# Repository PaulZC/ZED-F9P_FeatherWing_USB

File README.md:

# ZED-F9P FeatherWing USB

A GNSS FeatherWing incorporating the dual-band (L1 + L2) [u-blox ZED-F9P](https://www.u-blox.com/en/product/zed-f9p-module)

The board can be used stand-alone, powered and interfaced through the USB connector:

However, it is designed to mount on top of the [Adafruit Feather M0 Adalogger](https://www.adafruit.com/products/2796)
to form a very compact dual-band PPK data logger or RTK system:

This version provides access to the ZED-F9P's USB port. The [ZED-F9P_FeatherWing](https://github.com/PaulZC/ZED-F9P_FeatherWing) is a simpler version
with fewer components and a CR1220 back-up battery but without USB.

Based extensively on the [Adafruit Ultimate GPS FeatherWing](https://www.adafruit.com/product/3133) and the
[SparkFun GPS-RTK2 Board](https://www.sparkfun.com/products/15136)

If you don't want to make your own FeatherWing and want to use the SparkFun GPS-RTK2 Board instead, you can find a tutorial showing you how to do that
[here](https://github.com/PaulZC/F9P_RAWX_Logger)

See [LEARN.md](./LEARN.md) for more details

[ASSEMBLY.md](./ASSEMBLY.md) contains instructions on how to assemble the PCB

[PAIRING.md](./PAIRING.md) contains instructions on how to configure two SparkFun Bluetooth Mate Gold boards
as a bonded pair, to provide a 115200 Baud RTCM link

The Eagle files are available in the [Eagle folder](./Eagle)

The schematic is available [here](./Schematic.PNG)

The BOM is available [here](./BOM.pdf)

The PCB thickness should be 0.8mm: see the microstrip calculations on the [SparkFun schematic](https://cdn.sparkfun.com/assets/9/a/0/0/a/Qwiic_GPS-RTK2_-_ublox_ZED-F9P.pdf)

## Arduino Code

Two versions of the Arduino code can be found in the [Arduino folder](./Arduino):

- **RAWX_Logger_F9P** is very similar to the logger I wrote for the [NEO-M8T FeatherWing](https://github.com/PaulZC/NEO-M8T_GNSS_FeatherWing) but is substantially updated for the ZED-F9P. It does all of the message configuration via UART1. **PLEASE NOTE:** this example is out-of-date as it uses the old version of the SparkFun u-blox Library.

- **RAWX_Logger_F9P_I2C** uses **version 3.1.5** of the SparkFun u-blox GNSS library to do all of the message configuration via the I2C port instead of UART1. This makes
the code more efficient as it does not need to ignore the UBX ACK messages (on UART1) and can simply stream all data from UART1 to the SD card.

You can find instructions on how to install the Arduino IDE and the required libraries [here](https://github.com/PaulZC/F9P_RAWX_Logger/blob/master/SOFTWARE.md).

The code has three 'modes': Rover, Base and Survey_In. The mode is set via pins A0 and A3 by the [RAWX Logger Switches](https://github.com/PaulZC/RAWX_Logger_Switches). The RAWX
messages are logged to SD card in all three modes for post-processing with [rtklibexplorer's](https://rtklibexplorer.wordpress.com/) version of [RTKLIB](http://rtkexplorer.com/downloads/rtklib-code/).

You will find settings in the code to help with debugging should you need it. Uncomment the line which contains **#define DEBUG** to enable them.

## Updating the ZED-F9P firmware

u-blox released [version 1.12](https://www.u-blox.com/sites/default/files/UBX_F9_100_HPG_112_ZED_F9P.a26bfd58dfd11c233f8fdba6b99adc5a.bin) of the ZED-F9P firmware
on 12th July 2019. If you bought your device(s) before then, it would be beneficial to update. The update process is straight forward and can be done through
the Tools menu in [u-center](https://www.u-blox.com/en/product/u-center) **but the update can only be done through UART1. It will fail if you try to update through USB.**

The [Arduino folder](./Arduino) contains a sketch called ZED-F9P_Echo. This will turn the Adalogger into
a simple USB to UART pass-through which you can use to update the ZED-F9P using u-center. The code runs at **9600 Baud only** so you must tick the
_Use this baudrate for update_ box and select 9600 from the drop-down list. The advice on the u-blox portal seems to be to select the _Use chip erase_ option too.

Updating at 9600 Baud is very slow, but this is the only way to prevent Baud rate changes during the update. The Echo code is very simple and does not support
baud rate changes. If you want to update more quickly, you can use (e.g.) an FTDI TTL-232R-3V3 cable to connect to the UART1 pins instead of the Adalogger.

## Acknowledgements

This project would not have been possible without the open source designs kindly provided by both Adafruit and SparkFun. Their work is gratefully acknowledged.

Adafruit invests time and resources providing this open source design, please support Adafruit and open-source hardware by purchasing products from Adafruit!

Feel like supporting open source hardware? Buy a board from SparkFun!

## Licence

Please see [LICENSE.md](./LICENSE.md) for details.

Enjoy!

**_Paul_**

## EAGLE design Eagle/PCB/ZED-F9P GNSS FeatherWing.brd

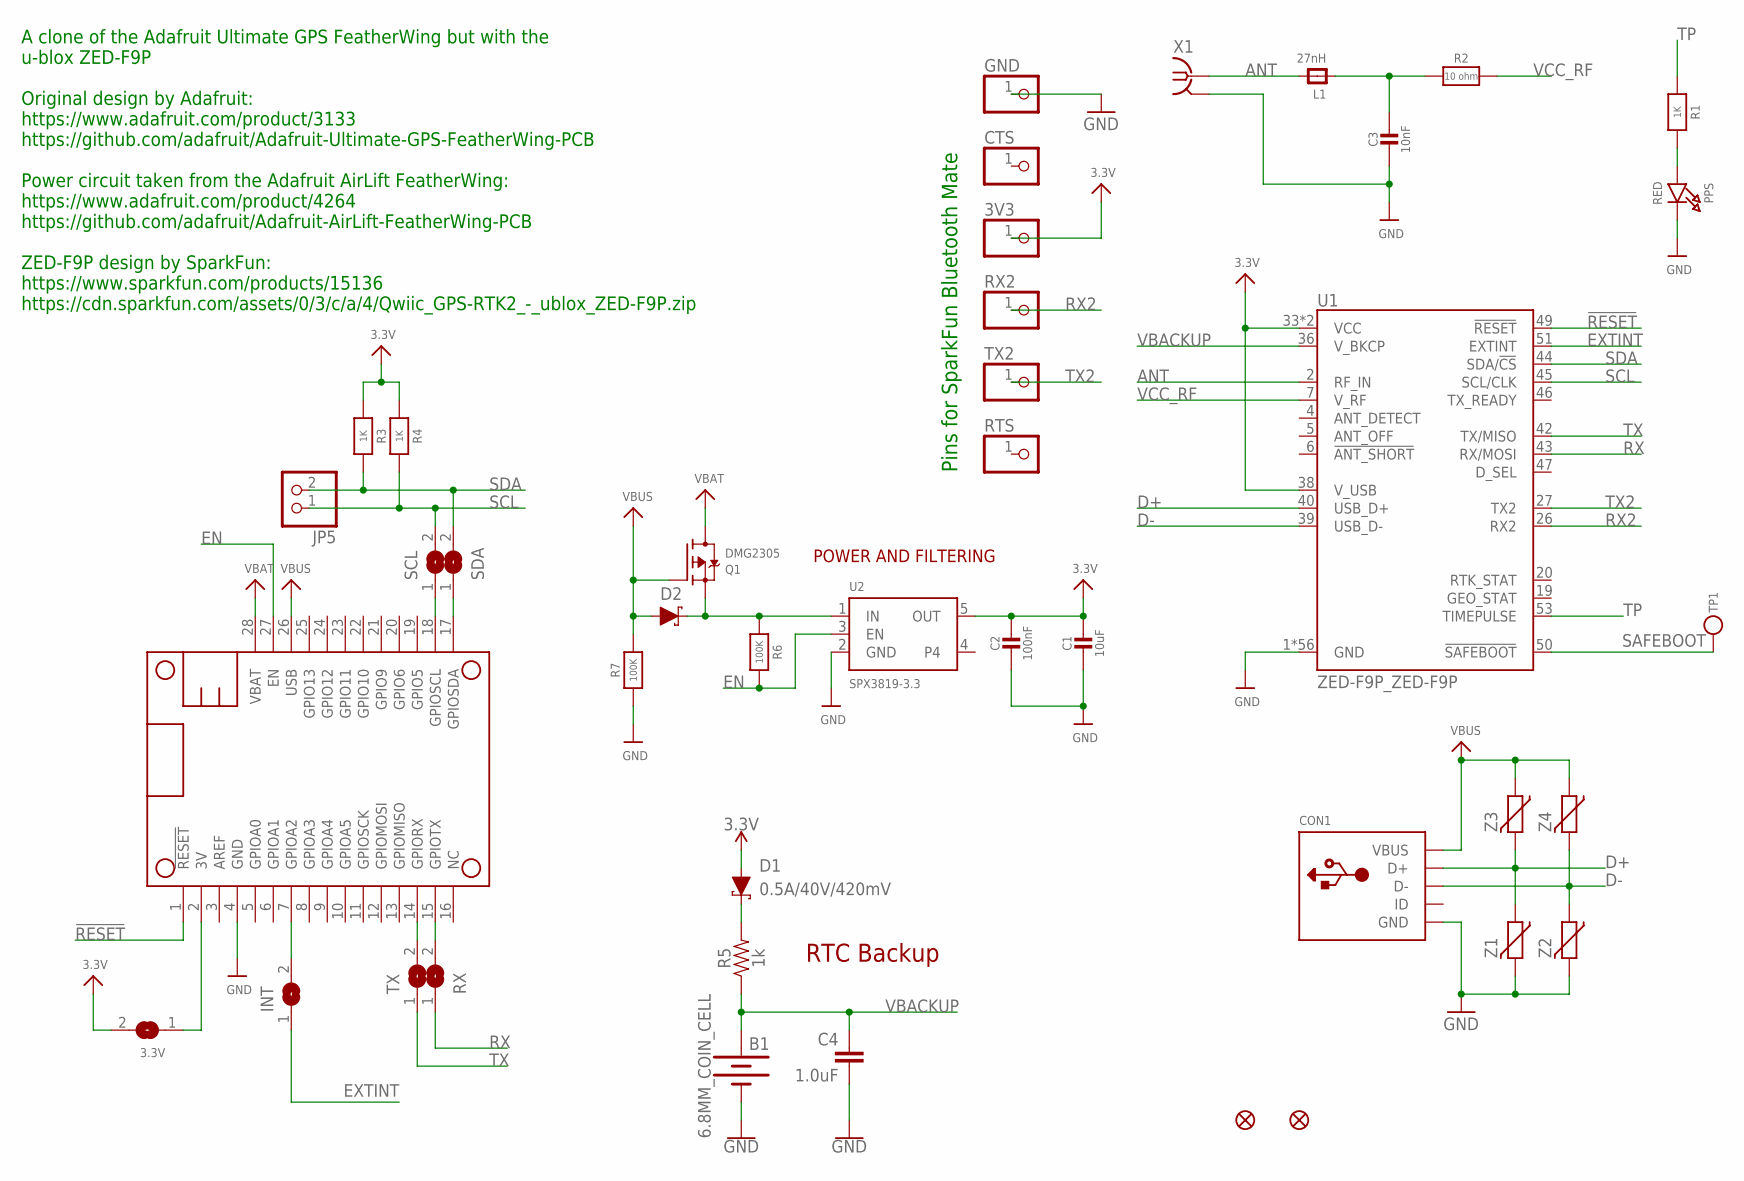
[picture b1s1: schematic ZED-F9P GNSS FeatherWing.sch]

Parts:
3.3V: SOLDERJUMPER; SOLDERJUMPER_ARROW_NOPASTE
3V3: PINHD-1X1; 1X01
B1: 6.8MM_COIN_CELL; BATTCON-6.8MM
C1: 10uF; 0805-NO
C2: 100nF; 0805-NO
C3: 10nF; 0805-NO
C4: 1.0uF; 0603
CON1: MICROBUILDER_USBFCI_10103594_CORRECTED; MICROBUILDER_FCI_10103594_CORRECTED
CTS: PINHD-1X1; 1X01
D1, D2: 0.5A/40V/420mV; SOD-323
FID1, FID2: FIDUCIAL""; FIDUCIAL_1MM
GND: PINHD-1X1; 1X01
INT: SOLDERJUMPERCLOSED; SOLDERJUMPER_CLOSEDWIRE
JP5: HEADER-1X2ROUND; 1X02_ROUND
L1: 27nH; 0805-NO
MS1: MICROBUILDER_FEATHERWINGMICROBUILDER_FEATHERWING_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; MICROBUILDER_FEATHERWING_HOLES
PPS: RED; CHIPLED_0805_NOOUTLINE
Q1: DMG2305; SOT23-R
R1, R3, R4: 1K; 0603-NO
R2: 10 ohm; 0805-NO
R5: 1k; 0603
R6, R7: 100K; 0603-NO
RTS: PINHD-1X1; 1X01
RX: SOLDERJUMPERCLOSED; SOLDERJUMPER_CLOSEDWIRE
RX2: PINHD-1X1; 1X01
SCL: SOLDERJUMPERCLOSED; SOLDERJUMPER_CLOSEDWIRE
SDA: SOLDERJUMPERCLOSED; SOLDERJUMPER_CLOSEDWIRE
TP1: TESTPOINTROUND1.5MM; TESTPOINT_ROUND_1.5MM
TX: SOLDERJUMPERCLOSED; SOLDERJUMPER_CLOSEDWIRE
TX2: PINHD-1X1; 1X01
U1: ZED-F9P_ZED-F9P
U2: SPX3819-3.3; SOT23-5
X1: SMA-142-0711-821/826; J502-ND-142-0711-821/826
Z1, Z2, Z3, Z4: CG0603MLC-05E; CT/CN0603

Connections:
3.3V: 3.3V.2, 3V3.1, C1.1, C2.1, D1.A, R3.1, R4.1, U1.33 (VCC), U1.34 (VCC), U1.38 (V_USB), U2.5 (OUT)
3V: 3.3V.1, MS1.2 (3V)
!RESET: MS1.1 (!RESET), U1.49 (!RESET!)
ANT: L1.2, U1.2 (RF_IN), X1.1
D+: CON1.D+, U1.40 (USB_D+), Z1.1, Z3.2
D-: CON1.D-, U1.39 (USB_D-), Z2.1, Z4.2
EN: MS1.27 (EN), R6.2, U2.3 (EN)
EXTINT: INT.1, U1.51 (EXTINT)
GND: B1.-, C1.2, C2.2, C3.2, C4.2, CON1.BASE@1 (GND), CON1.BASE@2 (GND), CON1.GND, CON1.SPRT@1 (GND), CON1.SPRT@2 (GND), CON1.SPRT@3 (GND), CON1.SPRT@4 (GND), GND.1, MS1.4 (GND), PPS.C, R7.1, U1.1 (GND), U1.3 (GND), U1.12 (GND), U1.14 (GND), U1.32 (GND), U1.37 (GND), U1.41 (GND), U1.48 (GND), U1.55 (GND), U1.56 (GND), U1.57 (GND), U1.58 (GND), U1.59 (GND), U1.60 (GND), U1.61 (GND), U1.62 (GND), U1.63 (GND), U1.64 (GND), U1.65 (GND), U1.66 (GND), U1.67 (GND), U1.68 (GND), U1.69 (GND), U1.70 (GND), U1.71 (GND), U1.72 (GND), U1.73 (GND), U1.74 (GND), U1.75 (GND), U1.76 (GND), U1.77 (GND), U1.78 (GND), U1.79 (GND), U1.80 (GND), U1.81 (GND), U1.82 (GND), U1.83 (GND), U1.84 (GND), U1.85 (GND), U1.86 (GND), U1.87 (GND), U1.88 (GND), U1.89 (GND), U1.90 (GND), U1.91 (GND), U1.92 (GND), U1.93 (GND), U1.94 (GND), U1.95 (GND), U1.96 (GND), U1.97 (GND), U1.98 (GND), U1.99 (GND), U1.100 (GND), U1.101 (GND), U1.102 (GND), U2.2 (GND), X1.G@1 (2), X1.G@2 (2), X1.G@3 (2), X1.G@4 (2), Z1.2, Z2.2
unnamed: MS1.18 (GPIOSCL), SCL.1
unnamed: PPS.A, R1.2
unnamed: MS1.17 (GPIOSDA), SDA.1
unnamed: C3.1, L1.1, R2.1
unnamed: MS1.14 (GPIORX), TX.2
unnamed: MS1.15 (GPIOTX), RX.2
unnamed: INT.2, MS1.7 (GPIOA2)
unnamed: D1.C, R5.2
unnamed: D2.C, Q1.2 (S), R6.1, U2.1 (IN)
RX: RX.1, U1.43 (RX/MOSI)
RX2: RX2.1, U1.26 (RX2)
SAFEBOOT: TP1.P$1, U1.50 (!SAFEBOOT!)
SCL: JP5.1, R4.2, SCL.2, U1.45 (SCL/CLK)
SDA: JP5.2, R3.2, SDA.2, U1.44 (SDA/!CS!)
TP: R1.1, U1.53 (TIMEPULSE)
TX: TX.1, U1.42 (TX/MISO)
TX2: TX2.1, U1.27 (TX2)
VBACKUP: B1.+, C4.1, R5.1, U1.36 (V_BKCP)
VBAT: MS1.28 (VBAT), Q1.3 (D)
VBUS: CON1.VBUS, D2.A, MS1.26 (USB), Q1.1 (G), R7.2, Z3.1, Z4.1
VCC_RF: R2.2, U1.7 (V_RF)

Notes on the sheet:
A clone of the Adafruit Ultimate GPS FeatherWing but with the u-blox ZED-F9P Original design by Adafruit: https://www.adafruit.com/product/3133 https://github.com/adafruit/Adafruit-Ultimate-GPS-FeatherWing-PCB Power circuit taken from the Adafruit AirLift FeatherWing: https://www.adafruit.com/produ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
Pins for SparkFun Bluetooth Mate
RTC Backup
POWER AND FILTERING

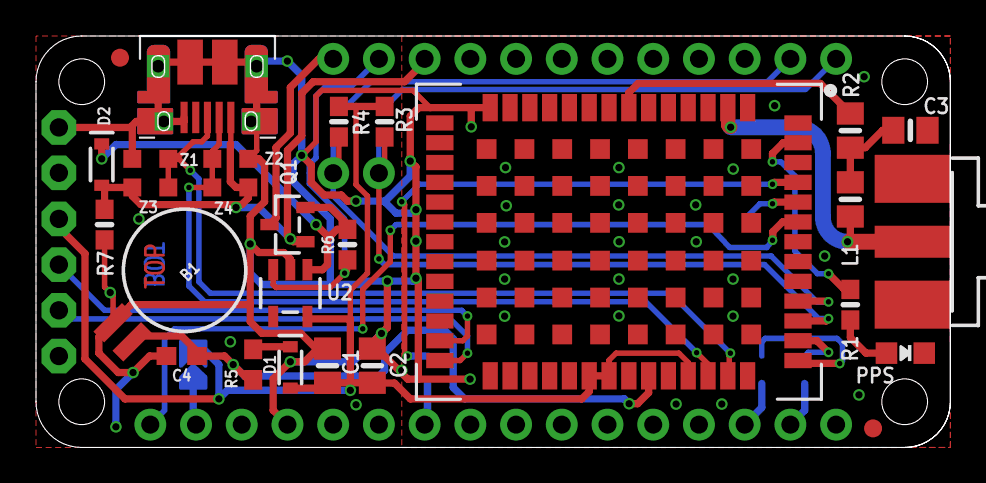
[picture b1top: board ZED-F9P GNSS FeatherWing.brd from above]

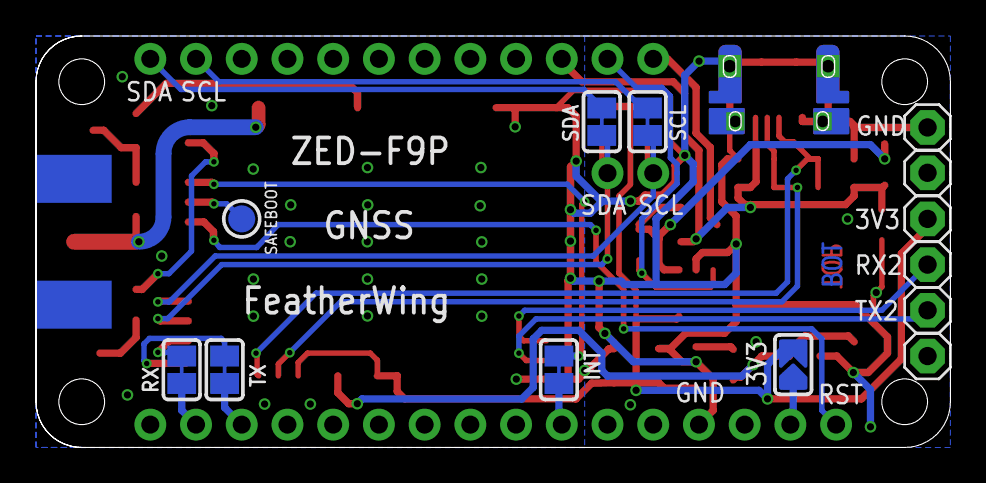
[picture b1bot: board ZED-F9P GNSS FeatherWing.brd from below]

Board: 2 copper layers, 50.7 x 22.8 mm, 42 parts (13 on the bottom side), 30 nets.

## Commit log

2019-06-11 Updated the power circuit
2019-06-12 Ready for manufacture
2019-06-14 As built
2019-06-27 Added as-built details
2019-06-27 Corrected the image types
2019-06-29 Added PAIRING info, placement jig and more images
2019-06-30 Added the images for LEARN.md
2019-06-30 Updated the solder paste instructions
2019-06-30 Added Assembly_11.JPG
2019-07-01 Minor corrections
2019-08-31 Firmware update. New I2C RAWX Logger.
    Added details of how to update the ZED-F9P firmware using ZED-F9P_Echo.
    Updated the I2C RAWX Logger code to use the new setVal functions in version 1.6 of the SparkFun u-blox library.
2019-08-31 Update RAWX_Logger_F9P_I2C.ino
    The I2C RAWX Logger now uses the SparkFun u-blox library to set the RTC. The Adafruit GPS library is no longer needed.
2019-11-08 Code can now 'disable' the timepulse LED
2022-10-01 Update license details
2024-07-15 Use relative md links
2024-07-15 Update u-blox GNSS
2024-07-15 Add delay for INTERVAL of 1440mins. Increase dwell
2024-07-15 Correct RTC comment

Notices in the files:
parts and their libraries:
SparkFun-Capacitors: Licensing: Creative Commons ShareAlike 4.0 International - https://creativecommons.org/licenses/by-sa/4.0
